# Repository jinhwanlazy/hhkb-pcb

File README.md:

This branch contains a variant that uses only 1.5u modifiers and alps switchs.
Also it doesn't cling to single sided artwork.

# Features
- Exactly same layout as original HHKB pro 2 (especially 6u space bar).
- Compatible with [TMK firmware](https://github.com/tmk/tmk_keyboard).
- Comaptible with any Cherry MX copy switches.
- Single sided board with SMD components
- Wide tracks(excellent for home fabrication)

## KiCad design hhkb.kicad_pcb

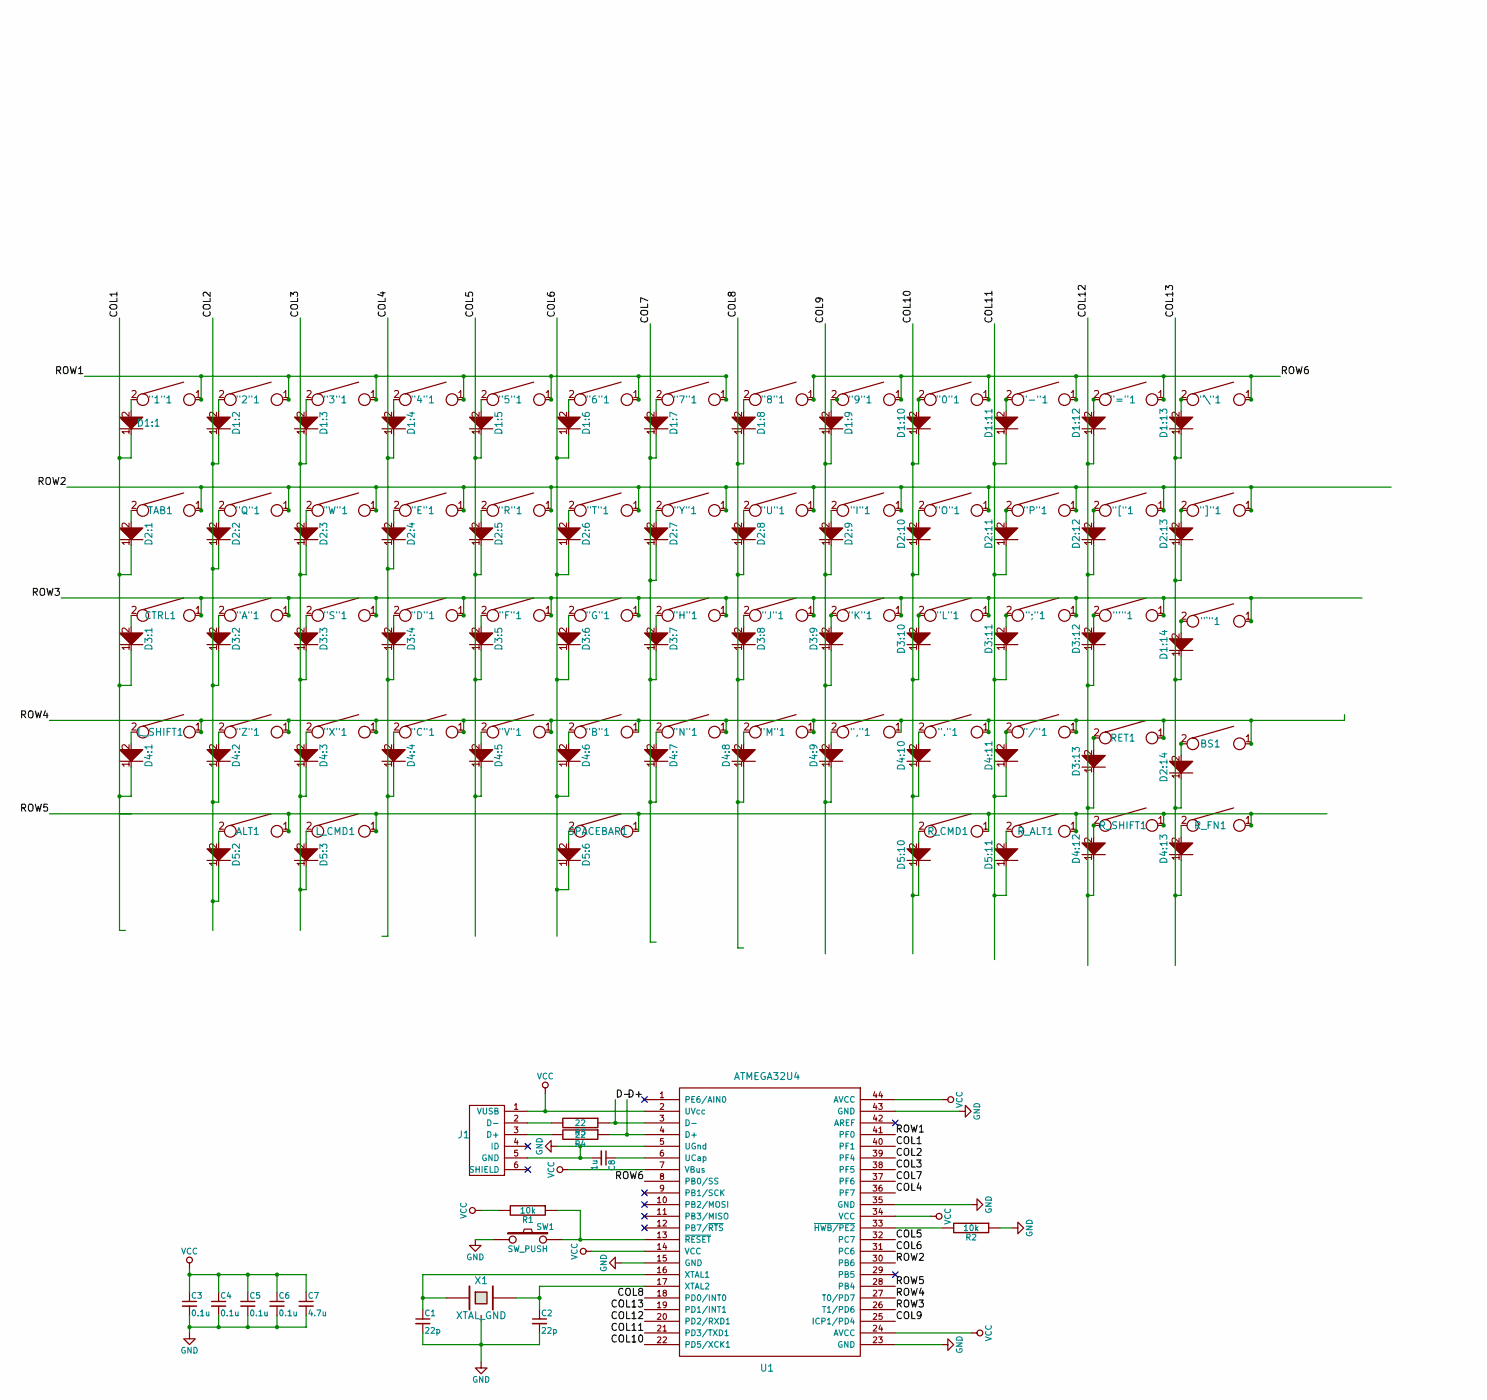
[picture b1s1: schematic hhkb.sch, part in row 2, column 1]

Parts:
"0"1, "1"1, "2"1, "3"1, "4"1, "5"1, "6"1, "7"1, "8"1, "9"1, "."1: KEYSW; Alps100
"'"1: KEYSW; Alps100
","1: KEYSW; Alps100
"-"1: KEYSW; Alps100
"/"1: KEYSW; Alps100
";"1: KEYSW; Alps100
"="1: KEYSW; Alps100
"A"1: KEYSW; Alps100
"B"1: KEYSW; Alps100
"C"1: KEYSW; Alps100
"D"1: KEYSW; Alps100
"E"1: KEYSW; Alps100
"F"1: KEYSW; Alps100
"G"1: KEYSW; Alps100
"H"1: KEYSW; Alps100
"I"1: KEYSW; Alps100
"J"1: KEYSW; Alps100
"K"1: KEYSW; Alps100
"L"1: KEYSW; Alps100
"M"1: KEYSW; Alps100
"N"1: KEYSW; Alps100
"O"1: KEYSW; Alps100
"P"1: KEYSW; Alps100
"Q"1: KEYSW; Alps100
"R"1: KEYSW; Alps100
"S"1: KEYSW; Alps100
"T"1: KEYSW; Alps100
"U"1: KEYSW; Alps100
"V"1: KEYSW; Alps100
"W"1: KEYSW; Alps100
"X"1: KEYSW; Alps100
"Y"1: KEYSW; Alps100
"Z"1: KEYSW; Alps100
"["1: KEYSW; Alps100
"\"1: KEYSW; Alps100
"]"1: KEYSW; Alps100
"`"1: KEYSW; Alps100
ALT1: KEYSW; Alps100
BS1: KEYSW; Alps150
C1, C2: 22p; C_0805_HandSoldering
C3, C4, C5, C6: 0.1u; C_0805_HandSoldering
C7: 4.7u; C_0805_HandSoldering
C8: 1u; C_0805_HandSoldering
CTRL1: KEYSW; Alps100
D1:1, D1:2, D1:3, D1:4, D1:5, D1:8, D1:9, D1:10, D1:11, D1:12, D2:1, D2:2, D2:3, D2:4, D2:5, D2:6, D2:7, D2:8, D2:9, D2:10, D2:11, D2:12, D2:13, D2:14, D3:1, D3:2, D3:3, D3:4, D3:5, D3:6, D3:7, D3:8, D3:9, D3:10, D3:11, D3:12, D3:13, D4:1, D4:2, D4:3, D4:4, D4:5, D4:6, D4:7, D4:8, D4:9, D4:10, D4:11, D4:12, D4:13, D5:2, D5:3, D5:6, D5:10, D5:11: D; D_T-1_P10.16mm_Horizontal
D1:6, D1:7, D1:13, D1:14: D; D_T-1_P5.08mm_Horizontal
J1: USB_mini_micro_B; USB_miniB_through_hole
L_CMD1: KEYSW; Alps150
L_SHIFT1: KEYSW; Alps150
R1, R2: 10k; R_0805_HandSoldering
R3, R4: 22; R_0805_HandSoldering
RET1: KEYSW; Alps150
R_ALT1: KEYSW; Alps100
R_CMD1: KEYSW; Alps150
R_FN1: KEYSW; Alps100
R_SHIFT1: KEYSW; Alps150
SPACEBAR1: KEYSW; Alps600
SW1: SW_PUSH; SW_SPST_TL3342
TAB1: KEYSW; Alps100
U1: ATMEGA32U4; TQFP-44_10x10mm_Pitch0.8mm
X1: XTAL_GND; FA-238

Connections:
/COL1: D1:1.1, D2:1.1, D3:1.1, D4:1.1, U1.40 (PF1)
/COL2: D1:2.1, D2:2.1, D3:2.1, D4:2.1, D5:2.1, U1.39 (PF4)
/COL3: D1:3.1, D2:3.1, D3:3.1, D4:3.1, D5:3.1, U1.38 (PF5)
/COL4: D1:4.1, D2:4.1, D3:4.1, D4:4.1, U1.36 (PF7)
/COL5: D1:5.1, D2:5.1, D3:5.1, D4:5.1, U1.32 (PC7)
/COL6: D1:6.1, D2:6.1, D3:6.1, D4:6.1, D5:6.1, U1.31 (PC6)
/COL7: D1:7.1, D2:7.1, D3:7.1, D4:7.1, U1.37 (PF6)
/COL8: D1:8.1, D2:8.1, D3:8.1, D4:8.1, U1.18 (PD0/INT0)
/COL9: D1:9.1, D2:9.1, D3:9.1, D4:9.1, U1.25 (ICP1/PD4)
/COL10: D1:10.1, D2:10.1, D3:10.1, D4:10.1, D5:10.1, U1.22 (PD5/XCK1)
/COL11: D1:11.1, D2:11.1, D3:11.1, D4:11.1, D5:11.1, U1.21 (PD3/TXD1)
/COL12: D1:12.1, D2:12.1, D3:12.1, D3:13.1, D4:12.1, U1.20 (PD2/RXD1)
/COL13: D1:13.1, D1:14.1, D2:13.1, D2:14.1, D4:13.1, U1.19 (PD1/INT1)
/D+: R4.1, U1.4 (D+)
/D-: R3.1, U1.3 (D-)
/ROW1: "1"1.1, "2"1.1, "3"1.1, "4"1.1, "5"1.1, "6"1.1, "7"1.1, U1.41 (PF0)
/ROW2: "E"1.1, "I"1.1, "O"1.1, "P"1.1, "Q"1.1, "R"1.1, "T"1.1, "U"1.1, "W"1.1, "Y"1.1, "["1.1, "]"1.1, TAB1.1, U1.30 (PB6)
/ROW3: "'"1.1, ";"1.1, "A"1.1, "D"1.1, "F"1.1, "G"1.1, "H"1.1, "J"1.1, "K"1.1, "L"1.1, "S"1.1, "`"1.1, CTRL1.1, U1.26 (T1/PD6)
/ROW4: ","1.1, "."1.1, "/"1.1, "B"1.1, "C"1.1, "M"1.1, "N"1.1, "V"1.1, "X"1.1, "Z"1.1, BS1.1, L_SHIFT1.1, RET1.1, U1.27 (T0/PD7)
/ROW5: ALT1.1, L_CMD1.1, R_ALT1.1, R_CMD1.1, R_FN1.1, R_SHIFT1.1, SPACEBAR1.1, U1.28 (PB4)
/ROW6: "0"1.1, "8"1.1, "9"1.1, "-"1.1, "="1.1, "\"1.1, U1.8 (PB0/SS)
GND: C1.2, C2.2, C3.2, C4.2, C5.2, C6.2, C7.2, C8.2, J1.5 (GND), R2.1, SW1.1, U1.5 (UGnd), U1.15 (GND), U1.23 (GND), U1.35 (GND), U1.43 (GND), X1.3
unnamed: "0"1.2, D1:10.2
unnamed: "1"1.2, D1:1.2
unnamed: "2"1.2, D1:2.2
unnamed: "3"1.2, D1:3.2
unnamed: "4"1.2, D1:4.2
unnamed: "5"1.2, D1:5.2
unnamed: "6"1.2, D1:6.2
unnamed: "7"1.2, D1:7.2
unnamed: "8"1.2, D1:8.2
unnamed: "9"1.2, D1:9.2
unnamed: "'"1.2, D3:12.2
unnamed: ","1.2, D4:9.2
unnamed: "-"1.2, D1:11.2
unnamed: "."1.2, D4:10.2
unnamed: "/"1.2, D4:11.2
unnamed: ";"1.2, D3:11.2
unnamed: "="1.2, D1:12.2
unnamed: "A"1.2, D3:2.2
unnamed: "B"1.2, D4:6.2
unnamed: "C"1.2, D4:4.2
unnamed: "D"1.2, D3:4.2
unnamed: "E"1.2, D2:4.2
unnamed: "F"1.2, D3:5.2
unnamed: "G"1.2, D3:6.2
unnamed: "H"1.2, D3:7.2
unnamed: "I"1.2, D2:9.2
unnamed: "J"1.2, D3:8.2
unnamed: "K"1.2, D3:9.2
unnamed: "L"1.2, D3:10.2
unnamed: "M"1.2, D4:8.2
unnamed: "N"1.2, D4:7.2
unnamed: "O"1.2, D2:10.2
unnamed: "P"1.2, D2:11.2
unnamed: "Q"1.2, D2:2.2
unnamed: "R"1.2, D2:5.2
unnamed: "S"1.2, D3:3.2
unnamed: "T"1.2, D2:6.2
unnamed: "U"1.2, D2:8.2
unnamed: "V"1.2, D4:5.2
unnamed: "W"1.2, D2:3.2
unnamed: "X"1.2, D4:3.2
unnamed: "Y"1.2, D2:7.2
unnamed: "Z"1.2, D4:2.2
unnamed: "["1.2, D2:12.2
unnamed: "\"1.2, D1:13.2
unnamed: "]"1.2, D2:13.2
unnamed: "`"1.2, D1:14.2
unnamed: ALT1.2, D5:2.2
unnamed: BS1.2, D2:14.2
unnamed: C1.1, U1.16 (XTAL1), X1.1
unnamed: C2.1, U1.17 (XTAL2), X1.2
unnamed: C8.1, U1.6 (UCap)
unnamed: CTRL1.2, D3:1.2
unnamed: D2:1.2, TAB1.2
unnamed: D3:13.2, RET1.2
unnamed: D4:1.2, L_SHIFT1.2
unnamed: D4:12.2, R_SHIFT1.2
unnamed: D4:13.2, R_FN1.2
unnamed: D5:3.2, L_CMD1.2
unnamed: D5:6.2, SPACEBAR1.2
unnamed: D5:10.2, R_CMD1.2
unnamed: D5:11.2, R_ALT1.2
unnamed: J1.2 (D-), R3.2
unnamed: J1.3 (D+), R4.2
unnamed: R1.1, SW1.2, U1.13 (~RESET)
unnamed: R2.2, U1.33 (~HWB/PE2)
VCC: C3.1, C4.1, C5.1, C6.1, C7.1, J1.1 (VUSB), R1.2, U1.2 (UVcc), U1.7 (VBus), U1.14 (VCC), U1.24 (AVCC), U1.34 (VCC), U1.44 (AVCC)

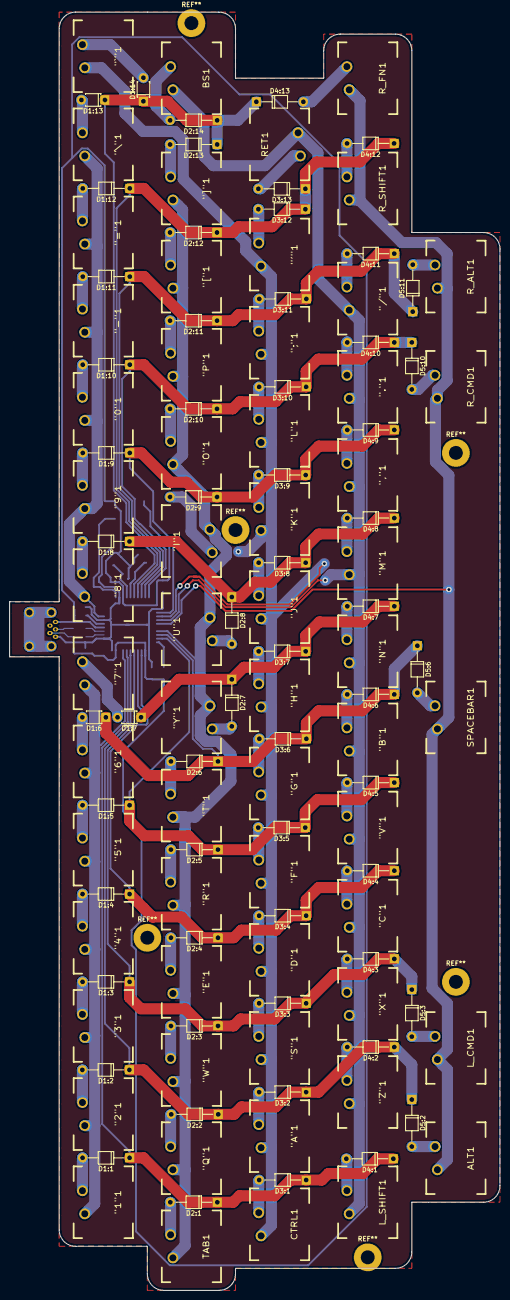
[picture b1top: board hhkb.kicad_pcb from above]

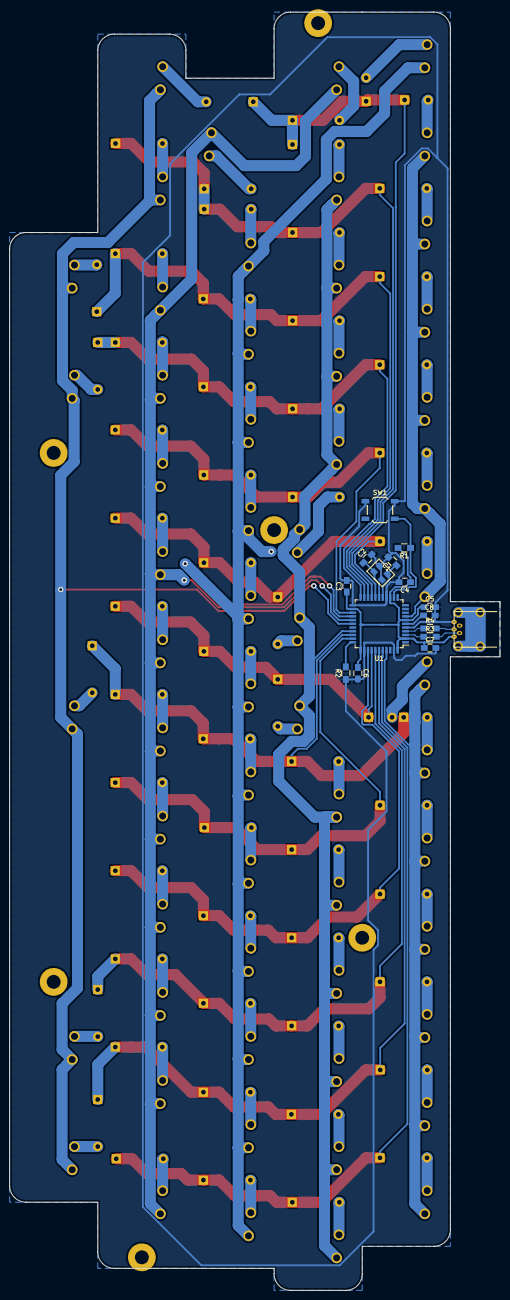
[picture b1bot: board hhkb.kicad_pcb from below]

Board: 2 copper layers, 106.0 x 276.2 mm, 134 parts (16 on the bottom side), 89 nets.

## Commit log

2017-03-28 init commit
2017-03-28 add readme
2017-03-28 rotate 90 degree
2017-03-28 ignore backup files
2017-03-28 change usb connector footprint
2017-03-29 add firmware
    note that fn layer is temporarily disabled due to error.
2017-03-30 optimize scanning
2017-03-30 edit readme
2017-03-30 fix wrong submodule
2017-03-30 seems syntax has changed?
2017-03-30 fix keymap macro
2017-03-30 match with official doc
2017-03-30 minimal vim like fn layer
    I might able to mimic all vim behaviors with keymap layers,
    but I decided to keep it simple.
    However, the insert key is an exception. It is never used without
    ctrl or shift, but also it is frequently used as a super set of
    ctrl-c/v.
2017-03-30 disable mouse key
2017-03-30 syntax change
2017-04-02 rm redundancy
2017-04-02 rm legacy
2017-04-03 disabling jtag solved all problems
2017-09-08 Add alps 100 footprint
2017-09-15 Add alps switch footprint
2017-09-15 Done
2017-09-18 Rm ground planes
2017-09-22 Rotate 90 deg to print.
2017-09-29 Via size to 0.8mm
2017-09-29 Regen gerbers
2017-09-29 Reduce milling area
2017-09-29 Set via size ot 1mm
2017-09-29 Update gerbers
2017-10-05 optimize path
2017-10-06 LCTRL now is a dual perpose key, works as additional ESC when tapped
2017-10-06 update firmware according to pcb
2017-10-06 Rework from scratch
2018-03-10 redraw
2018-03-10 Change usb footprint
2018-03-19 Gen gerbers
